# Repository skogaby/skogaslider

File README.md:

# skogaslider
Firmware, CAD, and PCB files for the skogaslider, an RP2040-based controller to simulate Chunithm's gameplay experience

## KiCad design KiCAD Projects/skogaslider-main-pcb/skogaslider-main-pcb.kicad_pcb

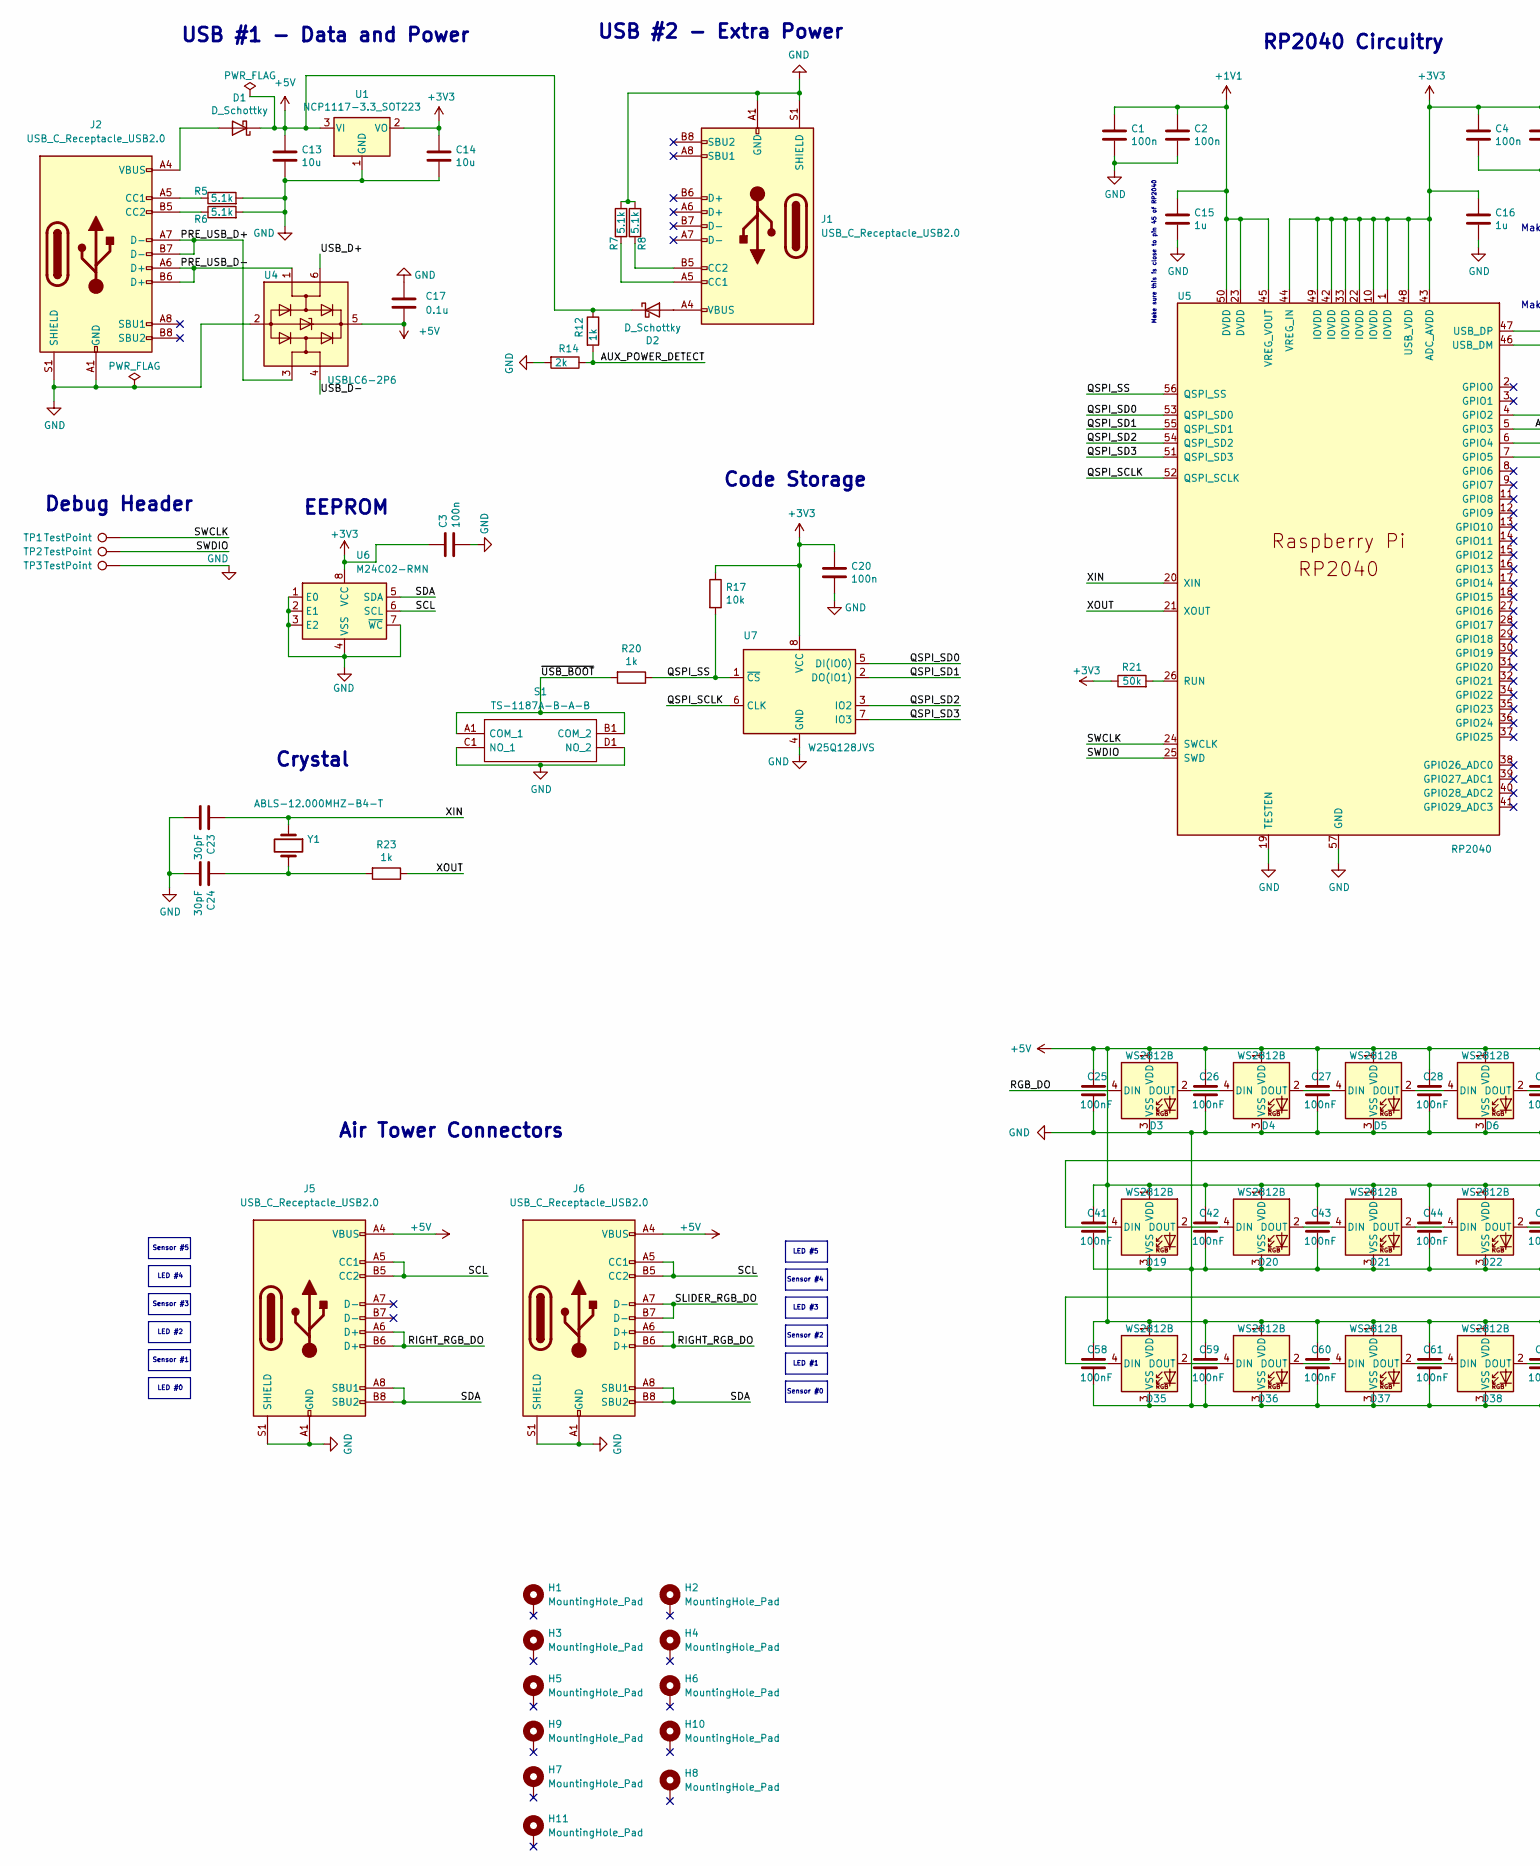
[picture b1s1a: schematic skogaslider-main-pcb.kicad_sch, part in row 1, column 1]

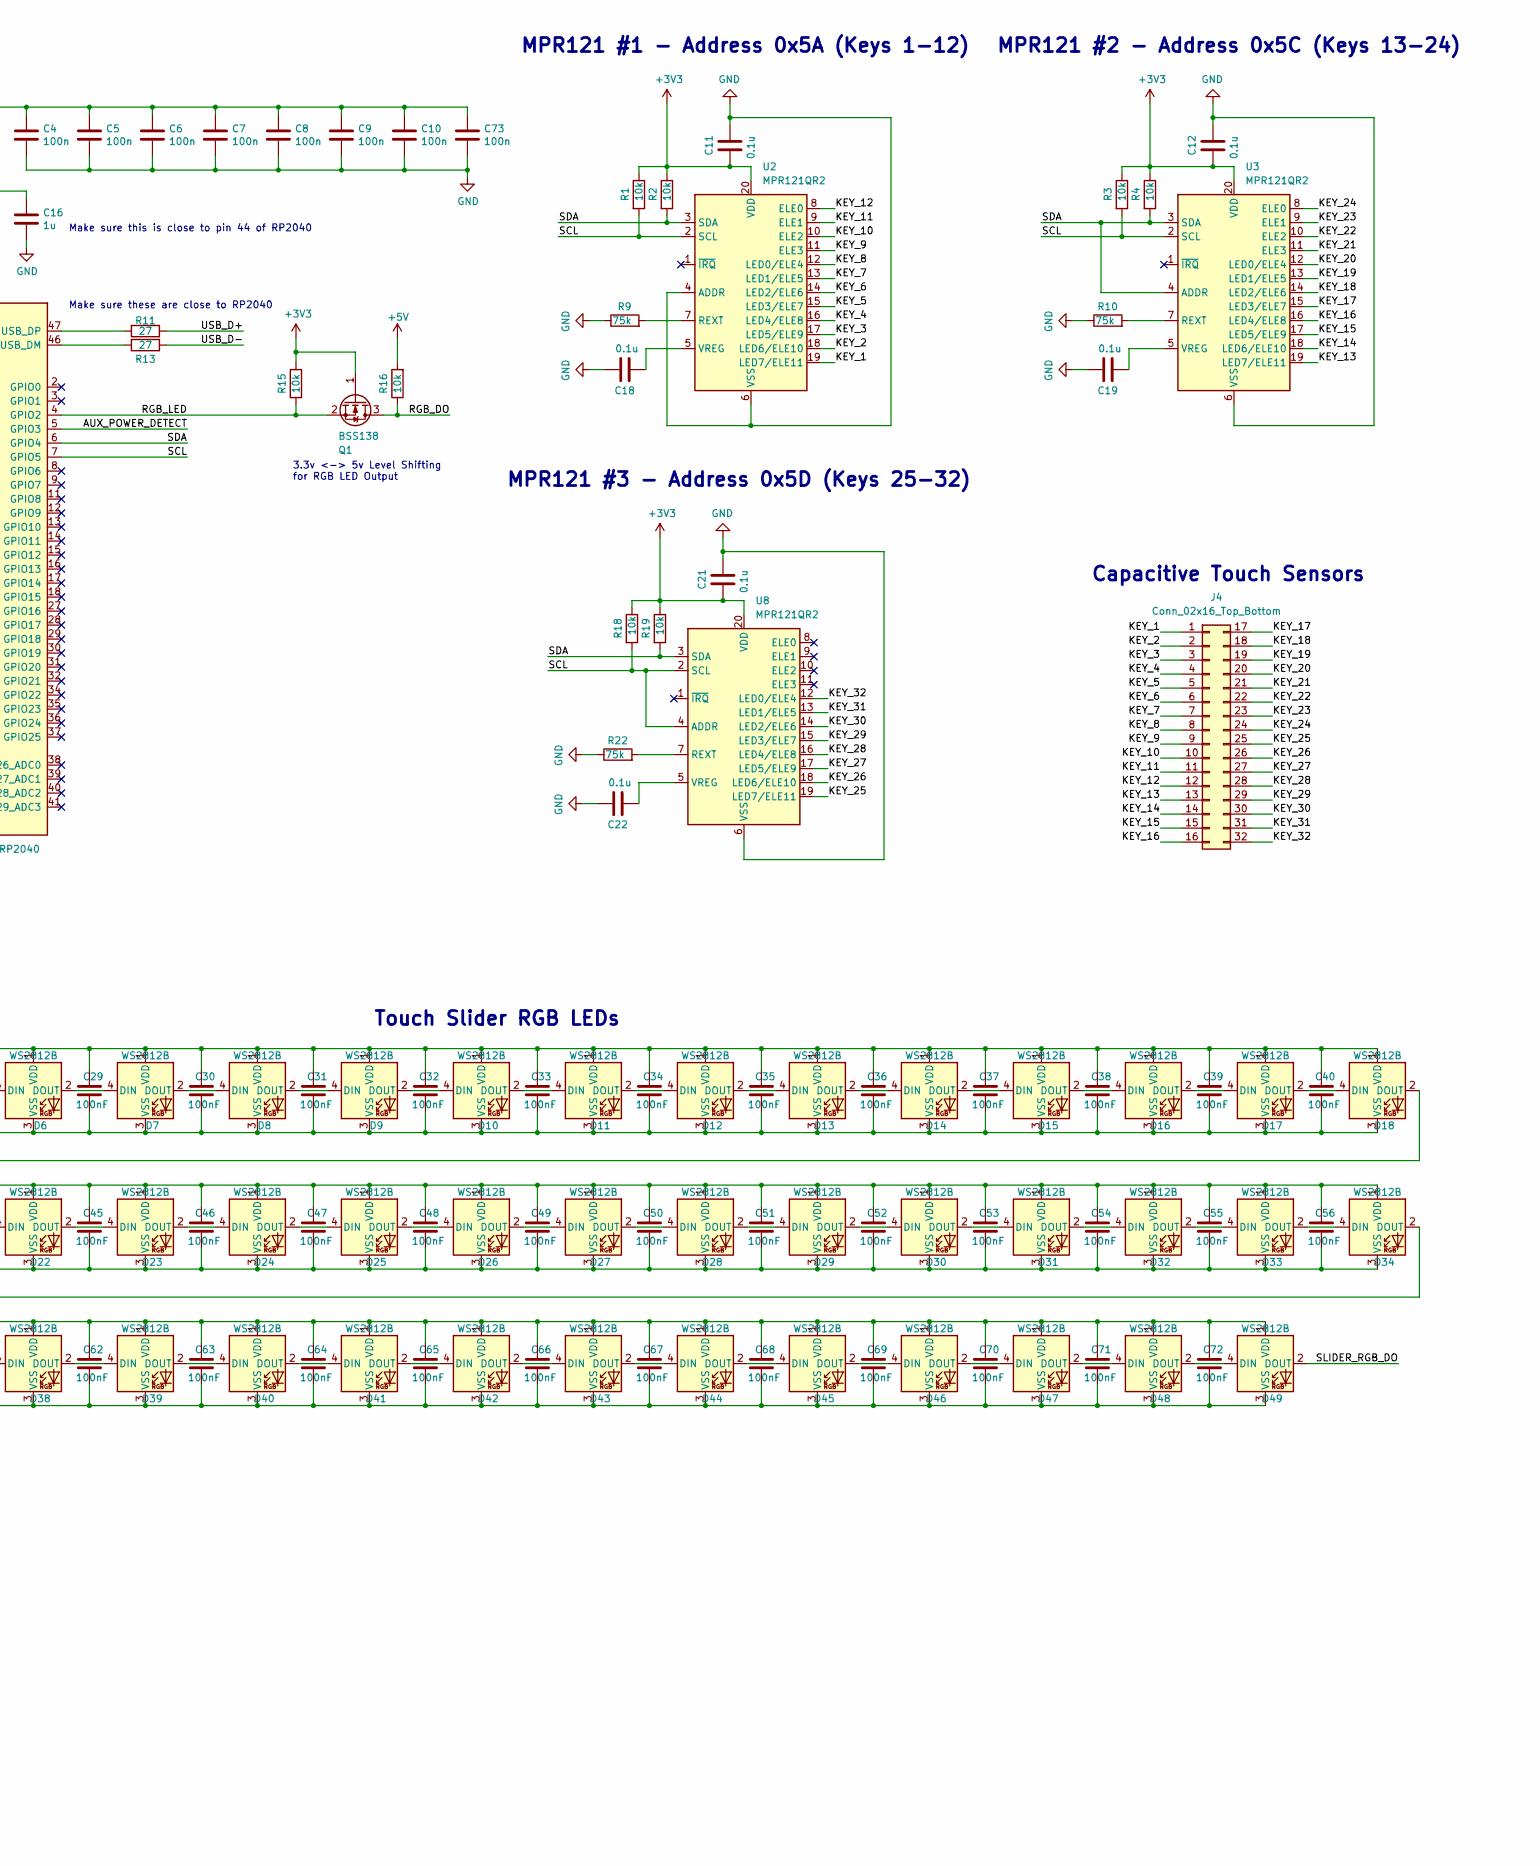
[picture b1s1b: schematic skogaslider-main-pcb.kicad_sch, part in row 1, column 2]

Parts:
C1, C2, C3, C4, C5, C6, C7, C8, C9, C10, C20, C73: 100n; C_0402_1005Metric
C11, C12, C17, C18, C19, C21, C22: 0.1u; C_0402_1005Metric
C13, C14: 10u; C_0805_2012Metric
C15, C16: 1u; C_0402_1005Metric
C23, C24: 30pF; C_0402_1005Metric
C25, C26, C27, C28, C29, C30, C31, C32, C33, C34, C35, C36, C37, C38, C39, C40, C41, C42, C43, C44, C45, C46, C47, C48, C49, C50, C51, C52, C53, C54, C55, C56, C58, C59, C60, C61, C62, C63, C64, C65, C66, C67, C68, C69, C70, C71, C72: 100nF; C_0402_1005Metric
D1, D2: D_Schottky; D_SMA; LCSC C22452
D3, D4, D5, D6, D7, D8, D9, D10, D11, D12, D13, D14, D15, D16, D17, D18, D19, D20, D21, D22, D23, D24, D25, D26, D27, D28, D29, D30, D31, D32, D33, D34, D35, D36, D37, D38, D39, D40, D41, D42, D43, D44, D45, D46, D47, D48, D49: WS2812B; WS2812B-4020
H1, H2, H3, H4, H5, H6, H7, H8, H9, H10, H11: MountingHole_Pad; MountingHole_3.2mm_M3_DIN965_Pad_TopBottom
J1, J2, J5, J6: USB_C_Receptacle_USB2.0; USB_C_Receptacle_HRO_TYPE-C-31-M-12
J4: Conn_02x16_Top_Bottom; Pads
Q1: BSS138; SOT-23
R1, R2, R3, R4, R15, R16, R17, R18, R19: 10k; R_0603_1608Metric
R5, R6, R7, R8: 5.1k; R_0603_1608Metric
R9, R10, R22: 75k; R_0603_1608Metric
R11, R13: 27; R_0603_1608Metric
R12, R20: 1k; R_0603_1608Metric
R14: 2k; R_0603_1608Metric
R21: 50k; R_0603_1608Metric
R23: 1k; R_0402_1005Metric
S1: TS-1187A-B-A-B; TS1187ABAB; Manufacturer_Part_Number TS-1187A-B-A-B
TP1, TP2, TP3: TestPoint; TestPoint_Pad_1.0x1.0mm
U1: NCP1117-3.3_SOT223; SOT-223-3_TabPin2
U2, U3, U8: MPR121QR2; UQFN-20_3x3mm_P0.4mm
U4: USBLC6-2P6; SOT-666
U5: RP2040; RP2040-QFN-56
U6: M24C02-RMN; SOIC-8_3.9x4.9mm_P1.27mm
U7: W25Q128JVS; SOIC-8_5.23x5.23mm_P1.27mm
Y1: ABLS-12.000MHZ-B4-T; Crystal_SMD_HC49-US

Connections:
+1V1: C1.1, C2.1, C15.1, U5.23 (DVDD), U5.45 (VREG_VOUT), U5.50 (DVDD)
+3V3: C3.1, C4.1, C5.1, C6.1, C7.1, C8.1, C9.1, C10.1, C11.2, C12.2, C14.1, C16.1, C20.1, C21.2, C73.1, Q1.1 (G), R1.1, R2.1, R3.1, R4.1, R15.2, R17.1, R18.1, R19.1, R21.1, U1.2 (VO), U2.20 (VDD), U3.20 (VDD), U5.1 (IOVDD), U5.10 (IOVDD), U5.22 (IOVDD), U5.33 (IOVDD), U5.42 (IOVDD), U5.43 (ADC_AVDD), U5.44 (VREG_IN), U5.48 (USB_VDD), U5.49 (IOVDD), U6.8 (VCC), U7.8 (VCC), U8.20 (VDD)
+5V: C13.1, C17.2, C25.1, C26.1, C27.1, C28.1, C29.1, C30.1, C31.1, C32.1, C33.1, C34.1, C35.1, C36.1, C37.1, C38.1, C39.1, C40.1, C41.1, C42.1, C43.1, C44.1, C45.1, C46.1, C47.1, C48.1, C49.1, C50.1, C51.1, C52.1, C53.1, C54.1, C55.1, C56.1, C58.1, C59.1, C60.1, C61.1, C62.1, C63.1, C64.1, C65.1, C66.1, C67.1, C68.1, C69.1, C70.1, C71.1, C72.1, D1.1 (K), D2.1 (K), D3.1 (VDD), D4.1 (VDD), D5.1 (VDD), D6.1 (VDD), D7.1 (VDD), D8.1 (VDD), D9.1 (VDD), D10.1 (VDD), D11.1 (VDD), D12.1 (VDD), D13.1 (VDD), D14.1 (VDD), D15.1 (VDD), D16.1 (VDD), D17.1 (VDD), D18.1 (VDD), D19.1 (VDD), D20.1 (VDD), D21.1 (VDD), D22.1 (VDD), D23.1 (VDD), D24.1 (VDD), D25.1 (VDD), D26.1 (VDD), D27.1 (VDD), D28.1 (VDD), D29.1 (VDD), D30.1 (VDD), D31.1 (VDD), D32.1 (VDD), D33.1 (VDD), D34.1 (VDD), D35.1 (VDD), D36.1 (VDD), D37.1 (VDD), D38.1 (VDD), D39.1 (VDD), D40.1 (VDD), D41.1 (VDD), D42.1 (VDD), D43.1 (VDD), D44.1 (VDD), D45.1 (VDD), D46.1 (VDD), D47.1 (VDD), D48.1 (VDD), D49.1 (VDD), J5.A4 (VBUS), J5.A9 (VBUS), J5.B4 (VBUS), J5.B9 (VBUS), J6.A4 (VBUS), J6.A9 (VBUS), J6.B4 (VBUS), J6.B9 (VBUS), R12.1, R16.2, U1.3 (VI), U4.5 (VBUS)
/AUX_POWER_DETECT: R12.2, R14.1, U5.5 (GPIO3)
/KEY_1: J4.1, U2.19 (LED7/ELE11)
/KEY_2: J4.2, U2.18 (LED6/ELE10)
/KEY_3: J4.3, U2.17 (LED5/ELE9)
/KEY_4: J4.4, U2.16 (LED4/ELE8)
/KEY_5: J4.5, U2.15 (LED3/ELE7)
/KEY_6: J4.6, U2.14 (LED2/ELE6)
/KEY_7: J4.7, U2.13 (LED1/ELE5)
/KEY_8: J4.8, U2.12 (LED0/ELE4)
/KEY_9: J4.9, U2.11 (ELE3)
/KEY_10: J4.10, U2.10 (ELE2)
/KEY_11: J4.11, U2.9 (ELE1)
/KEY_12: J4.12, U2.8 (ELE0)
/KEY_13: J4.13, U3.19 (LED7/ELE11)
/KEY_14: J4.14, U3.18 (LED6/ELE10)
/KEY_15: J4.15, U3.17 (LED5/ELE9)
/KEY_16: J4.16, U3.16 (LED4/ELE8)
/KEY_17: J4.17, U3.15 (LED3/ELE7)
/KEY_18: J4.18, U3.14 (LED2/ELE6)
/KEY_19: J4.19, U3.13 (LED1/ELE5)
/KEY_20: J4.20, U3.12 (LED0/ELE4)
/KEY_21: J4.21, U3.11 (ELE3)
/KEY_22: J4.22, U3.10 (ELE2)
/KEY_23: J4.23, U3.9 (ELE1)
/KEY_24: J4.24, U3.8 (ELE0)
/KEY_25: J4.25, U8.19 (LED7/ELE11)
/KEY_26: J4.26, U8.18 (LED6/ELE10)
/KEY_27: J4.27, U8.17 (LED5/ELE9)
/KEY_28: J4.28, U8.16 (LED4/ELE8)
/KEY_29: J4.29, U8.15 (LED3/ELE7)
/KEY_30: J4.30, U8.14 (LED2/ELE6)
/KEY_31: J4.31, U8.13 (LED1/ELE5)
/KEY_32: J4.32, U8.12 (LED0/ELE4)
/PRE_USB_D+: J2.A7 (D-), J2.B7 (D-), U4.3 (I/O2)
/PRE_USB_D-: J2.A6 (D+), J2.B6 (D+), U4.1 (I/O1)
/QSPI_SCLK: U5.52 (QSPI_SCLK), U7.6 (CLK)
/QSPI_SD0: U5.53 (QSPI_SD0), U7.5 (DI(IO0))
/QSPI_SD1: U5.55 (QSPI_SD1), U7.2 (DO(IO1))
/QSPI_SD2: U5.54 (QSPI_SD2), U7.3 (IO2)
/QSPI_SD3: U5.51 (QSPI_SD3), U7.7 (IO3)
/QSPI_SS: R17.2, R20.1, U5.56 (QSPI_SS), U7.1 (~CS)
/RGB_DO: D3.4 (DIN), Q1.3 (D), R16.1
/RGB_LED: Q1.2 (S), R15.1, U5.4 (GPIO2)
/RIGHT_RGB_DO: J5.A6 (D+), J5.B6 (D+), J6.A6 (D+), J6.B6 (D+)
/SCL: J5.A5 (CC1), J5.B5 (CC2), J6.A5 (CC1), J6.B5 (CC2), R1.2, R3.2, R18.2, U2.2 (SCL), U3.2 (SCL), U5.7 (GPIO5), U6.6 (SCL), U8.2 (SCL), U8.4 (ADDR)
/SDA: J5.A8 (SBU1), J5.B8 (SBU2), J6.A8 (SBU1), J6.B8 (SBU2), R2.2, R4.2, R19.2, U2.3 (SDA), U3.3 (SDA), U3.4 (ADDR), U5.6 (GPIO4), U6.5 (SDA), U8.3 (SDA)
/SLIDER_RGB_DO: D49.2 (DOUT), J6.A7 (D-), J6.B7 (D-)
/SWCLK: TP1.1, U5.24 (SWCLK)
/SWDIO: TP2.1, U5.25 (SWD)
/USB_D+: R11.1, U4.6 (I/O1)
/USB_D-: R13.1, U4.4 (I/O2)
/XIN: C23.1, U5.20 (XIN), Y1.1
/XOUT: R23.1, U5.21 (XOUT)
/~USB_BOOT: R20.2, S1.A1 (COM_1), S1.B1 (COM_2)
GND: C1.2, C2.2, C3.2, C4.2, C5.2, C6.2, C7.2, C8.2, C9.2, C10.2, C11.1, C12.1, C13.2, C14.2, C15.2, C16.2, C17.1, C18.1, C19.1, C20.2, C21.1, C22.1, C23.2, C24.2, C25.2, C26.2, C27.2, C28.2, C29.2, C30.2, C31.2, C32.2, C33.2, C34.2, C35.2, C36.2, C37.2, C38.2, C39.2, C40.2, C41.2, C42.2, C43.2, C44.2, C45.2, C46.2, C47.2, C48.2, C49.2, C50.2, C51.2, C52.2, C53.2, C54.2, C55.2, C56.2, C58.2, C59.2, C60.2, C61.2, C62.2, C63.2, C64.2, C65.2, C66.2, C67.2, C68.2, C69.2, C70.2, C71.2, C72.2, C73.2, D3.3 (VSS), D4.3 (VSS), D5.3 (VSS), D6.3 (VSS), D7.3 (VSS), D8.3 (VSS), D9.3 (VSS), D10.3 (VSS), D11.3 (VSS), D12.3 (VSS), D13.3 (VSS), D14.3 (VSS), D15.3 (VSS), D16.3 (VSS), D17.3 (VSS), D18.3 (VSS), D19.3 (VSS), D20.3 (VSS), D21.3 (VSS), D22.3 (VSS), D23.3 (VSS), D24.3 (VSS), D25.3 (VSS), D26.3 (VSS), D27.3 (VSS), D28.3 (VSS), D29.3 (VSS), D30.3 (VSS), D31.3 (VSS), D32.3 (VSS), D33.3 (VSS), D34.3 (VSS), D35.3 (VSS), D36.3 (VSS), D37.3 (VSS), D38.3 (VSS), D39.3 (VSS), D40.3 (VSS), D41.3 (VSS), D42.3 (VSS), D43.3 (VSS), D44.3 (VSS), D45.3 (VSS), D46.3 (VSS), D47.3 (VSS), D48.3 (VSS), D49.3 (VSS), J1.A1 (GND), J1.A12 (GND), J1.B1 (GND), J1.B12 (GND), J1.S1 (SHIELD), J2.A1 (GND), J2.A12 (GND), J2.B1 (GND), J2.B12 (GND), J2.S1 (SHIELD), J5.A1 (GND), J5.A12 (GND), J5.B1 (GND), J5.B12 (GND), J5.S1 (SHIELD), J6.A1 (GND), J6.A12 (GND), J6.B1 (GND), J6.B12 (GND), J6.S1 (SHIELD), R5.2, R6.2, R7.2, R8.2, R9.1, R10.1, R14.2, R22.1, S1.C1 (NO_1), S1.D1 (NO_2), TP3.1, U1.1 (GND), U2.4 (ADDR), U2.6 (VSS), U3.6 (VSS), U4.2 (GND), U5.19 (TESTEN), U5.57 (GND), U6.1 (E0), U6.2 (E1), U6.3 (E2), U6.4 (VSS), U6.7 (~WC), U7.4 (GND), U8.6 (VSS)
unnamed: C18.2, U2.5 (VREG)
unnamed: C19.2, U3.5 (VREG)
unnamed: C22.2, U8.5 (VREG)
unnamed: C24.1, R23.2, Y1.2
unnamed: D1.2 (A), J2.A4 (VBUS), J2.A9 (VBUS), J2.B4 (VBUS), J2.B9 (VBUS)
unnamed: D2.2 (A), J1.A4 (VBUS), J1.A9 (VBUS), J1.B4 (VBUS), J1.B9 (VBUS)
unnamed: D3.2 (DOUT), D4.4 (DIN)
unnamed: D4.2 (DOUT), D5.4 (DIN)
unnamed: D5.2 (DOUT), D6.4 (DIN)
unnamed: D6.2 (DOUT), D7.4 (DIN)
unnamed: D7.2 (DOUT), D8.4 (DIN)
unnamed: D8.2 (DOUT), D9.4 (DIN)
unnamed: D10.2 (DOUT), D11.4 (DIN)
unnamed: D9.2 (DOUT), D10.4 (DIN)
unnamed: D11.2 (DOUT), D12.4 (DIN)
unnamed: D12.2 (DOUT), D13.4 (DIN)
unnamed: D13.2 (DOUT), D14.4 (DIN)
unnamed: D14.2 (DOUT), D15.4 (DIN)
unnamed: D15.2 (DOUT), D16.4 (DIN)
unnamed: D16.2 (DOUT), D17.4 (DIN)
unnamed: D17.2 (DOUT), D18.4 (DIN)
unnamed: D18.2 (DOUT), D19.4 (DIN)
unnamed: D19.2 (DOUT), D20.4 (DIN)
unnamed: D20.2 (DOUT), D21.4 (DIN)
unnamed: D21.2 (DOUT), D22.4 (DIN)
unnamed: D22.2 (DOUT), D23.4 (DIN)
unnamed: D23.2 (DOUT), D24.4 (DIN)
unnamed: D24.2 (DOUT), D25.4 (DIN)
unnamed: D25.2 (DOUT), D26.4 (DIN)
unnamed: D26.2 (DOUT), D27.4 (DIN)
unnamed: D27.2 (DOUT), D28.4 (DIN)
unnamed: D28.2 (DOUT), D29.4 (DIN)
unnamed: D29.2 (DOUT), D30.4 (DIN)
unnamed: D30.2 (DOUT), D31.4 (DIN)
unnamed: D31.2 (DOUT), D32.4 (DIN)
unnamed: D32.2 (DOUT), D33.4 (DIN)
unnamed: D33.2 (DOUT), D34.4 (DIN)
unnamed: D34.2 (DOUT), D35.4 (DIN)
unnamed: D35.2 (DOUT), D36.4 (DIN)
unnamed: D36.2 (DOUT), D37.4 (DIN)
unnamed: D37.2 (DOUT), D38.4 (DIN)
unnamed: D38.2 (DOUT), D39.4 (DIN)
unnamed: D39.2 (DOUT), D40.4 (DIN)
unnamed: D40.2 (DOUT), D41.4 (DIN)
unnamed: D41.2 (DOUT), D42.4 (DIN)
unnamed: D42.2 (DOUT), D43.4 (DIN)
unnamed: D43.2 (DOUT), D44.4 (DIN)
unnamed: D44.2 (DOUT), D45.4 (DIN)
unnamed: D45.2 (DOUT), D46.4 (DIN)
unnamed: D46.2 (DOUT), D47.4 (DIN)
unnamed: D47.2 (DOUT), D48.4 (DIN)
unnamed: D48.2 (DOUT), D49.4 (DIN)
unnamed: J1.A5 (CC1), R7.1
unnamed: J1.B5 (CC2), R8.1
unnamed: J2.A5 (CC1), R5.1
unnamed: J2.B5 (CC2), R6.1
unnamed: R9.2, U2.7 (REXT)
unnamed: R10.2, U3.7 (REXT)
unnamed: R11.2, U5.47 (USB_DP)
unnamed: R13.2, U5.46 (USB_DM)
unnamed: R21.2, U5.26 (RUN)
unnamed: R22.2, U8.7 (REXT)

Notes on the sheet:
USB #2 - Extra Power
LED #4
Sensor #3
RP2040 Circuitry
Touch Slider RGB LEDs
LED #2
Make sure this is close to pin 45 of RP2040
Code Storage
Sensor #0
Sensor #1
Capacitive Touch Sensors
Crystal
USB #1 - Data and Power
Sensor #5
LED #5
MPR121 #1 - Address 0x5A (Keys 1-12)
LED #1
LED #3
MPR121 #2 - Address 0x5C (Keys 13-24)
LED #0
Debug Header
Air Tower Connectors
Sensor #4
Make sure this is close to pin 44 of RP2040
Sensor #2
3.3v <-> 5v Level Shifting for RGB LED Output
Make sure these are close to RP2040
MPR121 #3 - Address 0x5D (Keys 25-32)
EEPROM

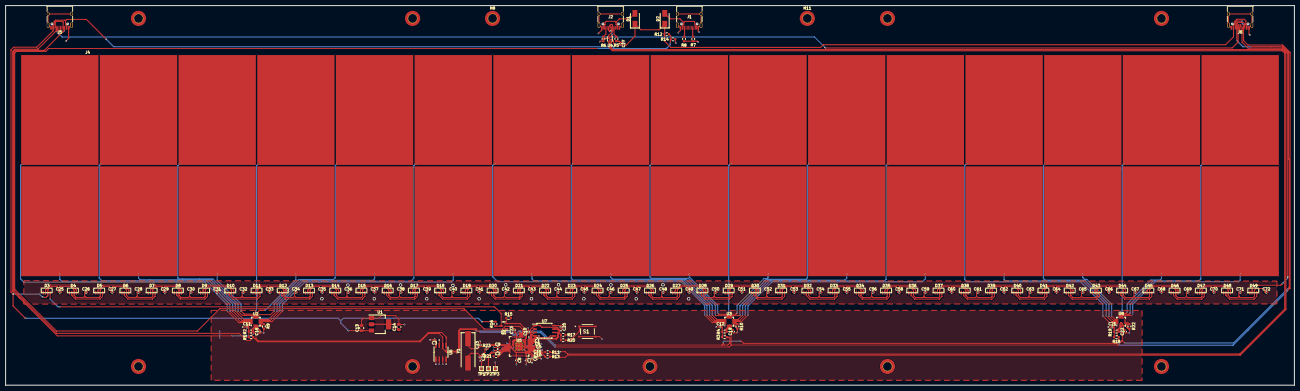
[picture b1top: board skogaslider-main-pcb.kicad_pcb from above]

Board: 2 copper layers, 475.0 x 139.9 mm, 174 parts (0 on the bottom side), 120 nets.

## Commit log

2022-06-06 Initial commit, adding the preliminary schematic for the main slider PCB. Still need to do the air tower schematics, plus the PCB layouts, etc.
2022-06-06 Almost final schematic for the main slider, minus a couple of small tweaks. Significant progress on slider board layout. MPR121 layouts are essentially complete minus the key wiring. USB C ports and 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
2022-06-07 More layout progress for the main slider PCB
2022-06-14 PCB layout is almost complete for the mainboard, minus the board cuts, mounting holes, and power/ground planes
2022-06-14 First pass of the mainboard layout is done, besides art and mounting holes
2022-06-15 Added JLCPCB part number mappings for everything, so we can export this via the jlcpcb plugin to order, once everything is finalized.
2022-06-23 v0.1 of the slider PCB is likely complete, waiting for a prototype order to arrive before making any real changes.
2022-07-04 Commit the first pass of the RP2040 firmware. Right now all it does is read the MPR121s and do reactive lighting; no outputs, air towers, HID lights, etc. yet.
2022-07-04 Doing some re-arranging of the firmware source, and experimenting with multicore programming
2022-07-04 Have the primary core keep track of whether the state has changed, rather than keep track of it within the TouchSlider class, since the scans for TouchSlider aren't coupled to when the states are act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
2022-07-09 Remove some unneeded code from PicoLED, and adding rudimentary keyboard output (still needs a production refactor)
2022-07-09 Add a CDC interface to the tinyUSB config so we can get serial output alongside USB HID output. Requires pico-sdk 1.4.0+ to work correctly.
2022-07-09 Shift around some of the responsibilities of the two cores, so that interacting with the slider does not drop the output rate or the scan rate.
2022-07-11 Reorganizing some of the firmware code and making it adhere to the naming conventions the SDK uses, for consistency.
2022-07-12 Implement a proper UsbOutput class for handling keyboard output. Limit the rate of LED strip updates to 250Hz (1/4 of the keyboard output rate)
2022-07-12 Small typo fixes
2022-07-15 First pass implementation of the SEGA slider protocol for Chunithm/Project Diva. Still need to wire up serial and pass the data back and forth, but the protocol logic is in place.
2022-07-15 Start reading and processing responses for serial packets that are AC protocol (untested)
2022-07-15 Attempting to fix the slider AC protocol communications, still fixing some bugs with serial processing
2022-07-15 Small fix to make the HWInfo packet correct
2022-07-15 Attempting to fix serial communications by transmitting and reading one byte at a time, still working out some bugs though
2022-07-16 The SEGA slider protocol is finally working correctly, but it seems to get slower over time, might need to change how serial is read
2022-07-16 Place a limit on how often we send AC protocol touch reports when auto scan is enabled, so we don't flood the USB buffers
2022-07-16 Small fixes for logging, and reading LED brightnesses correctly.
2022-07-19 Separate out serial reading logic into its own separate class which can handle multiple different kinds of packets. Begin to stub out the implementation for emulating the 15093-06 LED boards, for air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
2022-07-19 Implement a simple 5-second timeout for serial packets in AC protocol mode. If no serial packets are received in 5 seconds, auto-reporting is disabled for touch reports.
2022-07-19 Implement the first pass logic for reading LED packets, still need to implement the protocol processing itself.
2022-07-19 Stub out the protocol handlers for the LED boards, still need to fill out the responses
2022-07-19 Add 2 more CDC endpoints for LED 15093-06 emulation (1 endpoint for each board). This brings us to 4 CDC endpoints (stdio, slider, 2x LED)
2022-07-21 First pass implementation of the 15093-06 LED board protocol emulation. This is still untested for now.
2022-07-21 Keep track of how often we're updating air tower lights
2022-07-21 Simplify the implementation for the firmware sum
2022-07-22 Small fix for the Pico SDK path resolution
2022-07-23 Fix LED board emulation. Now slider + dual LED board emulation works perfectly at the same time
2022-07-23 Cut down on the number of static packet structures in the SegaSlider class to just a single response struct.
2022-07-23 Add a utility protocol command for the LED board emulation to get which side the board is for. This will be used for a utility desktop application to determine which COM port is which emulated device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
2022-07-31 Fix a bug in the slider LED report handling, and add handlers for slider commands 0x09 and 0x0A
2022-11-13 New revision of the mainboard schematic and layout. Switched the air towers from HDMI to USB-C, and made them use the I2C bus for communication to reduce the number of pins
2022-11-14 Fix up the top edge of the board so it fits within the controller CAD, and add more mounting holes.
2022-11-17 Minor revision of the slider PCB to re-arrange the mounting holes to fit the CAD better.
